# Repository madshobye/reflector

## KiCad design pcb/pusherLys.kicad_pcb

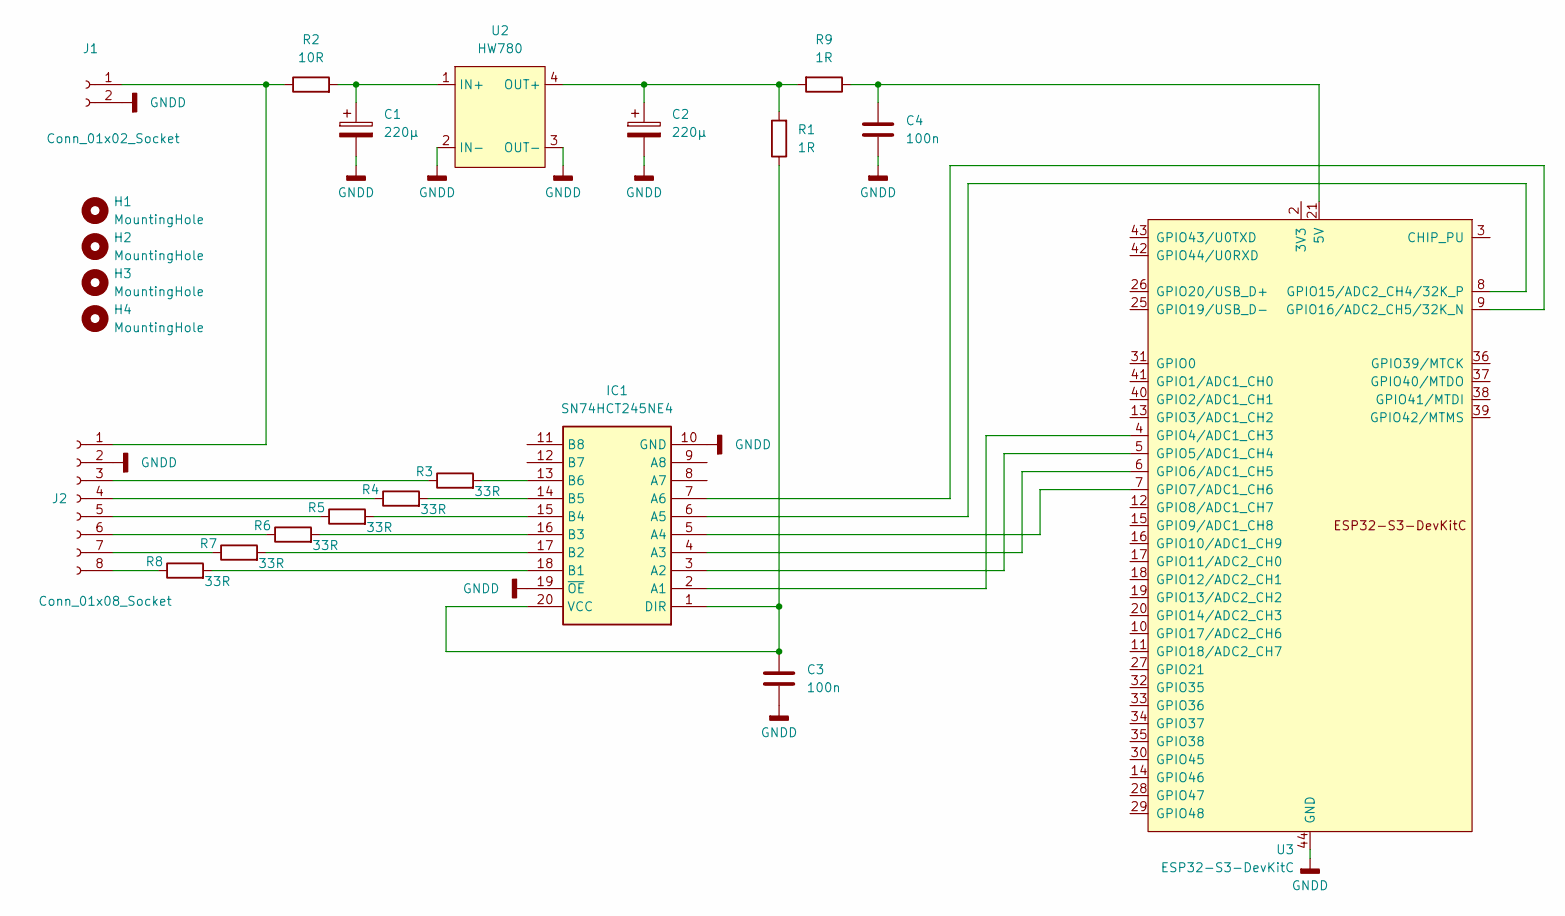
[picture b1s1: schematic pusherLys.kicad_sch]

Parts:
C1, C2: 220µ; CP_Radial_D8.0mm_P5.00mm
C3, C4: 100n; C_Disc_D5.0mm_W2.5mm_P5.00mm
H1, H2, H3, H4: MountingHole; MountingHole_3.5mm
IC1: SN74HCT245NE4; DIP-20_W7.62mm_LongPads; Mouser Part Number 595-SN74HCT245NE4
J1: Conn_01x02_Socket; TerminalBlock_MetzConnect_Type011_RT05502HBLC_1x02_P5.00mm_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
J2: Conn_01x08_Socket; TerminalBlock_MaiXu_MX126-5.0-08P_1x08_P5.00mm
R1, R9: 1R; R_Axial_DIN0207_L6.3mm_D2.5mm_P10.16mm_Horizontal
R2: 10R; R_Axial_DIN0207_L6.3mm_D2.5mm_P10.16mm_Horizontal
R3, R4, R5, R6, R7, R8: 33R; R_Axial_DIN0207_L6.3mm_D2.5mm_P10.16mm_Horizontal
U2: HW780
U3: ESP32-S3-DevKitC; ESP32-S3-DevKitC_WIDE

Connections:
GNDD: C1.2, C2.2, C3.2, C4.2, IC1.10 (GND), IC1.19 (~OE), J1.2, J2.2, U2.2 (IN-), U2.3 (OUT-), U3.22 (GND), U3.23 (GND), U3.24 (GND), U3.44 (GND)
unnamed: IC1.2 (A1), U3.4 (GPIO4/ADC1_CH3)
unnamed: IC1.3 (A2), U3.5 (GPIO5/ADC1_CH4)
unnamed: IC1.4 (A3), U3.6 (GPIO6/ADC1_CH5)
unnamed: IC1.5 (A4), U3.7 (GPIO7/ADC1_CH6)
unnamed: IC1.6 (A5), U3.8 (GPIO15/ADC2_CH4/32K_P)
unnamed: IC1.7 (A6), U3.9 (GPIO16/ADC2_CH5/32K_N)
unnamed: IC1.18 (B1), R8.2
unnamed: IC1.17 (B2), R7.2
unnamed: IC1.16 (B3), R6.2
unnamed: IC1.15 (B4), R5.2
unnamed: IC1.14 (B5), R4.2
unnamed: IC1.13 (B6), R3.2
unnamed: C3.1, IC1.1 (DIR), IC1.20 (VCC), R1.1
unnamed: J1.1, J2.1, R2.1
unnamed: J2.3, R3.1
unnamed: J2.4, R4.1
unnamed: J2.5, R5.1
unnamed: J2.6, R6.1
unnamed: J2.7, R7.1
unnamed: J2.8, R8.1
unnamed: C1.1, R2.2, U2.1 (IN+)
unnamed: C2.1, R1.2, R9.2, U2.4 (OUT+)
unnamed: U3.1 (3V3), U3.2 (3V3)
unnamed: C4.1, R9.1, U3.21 (5V)

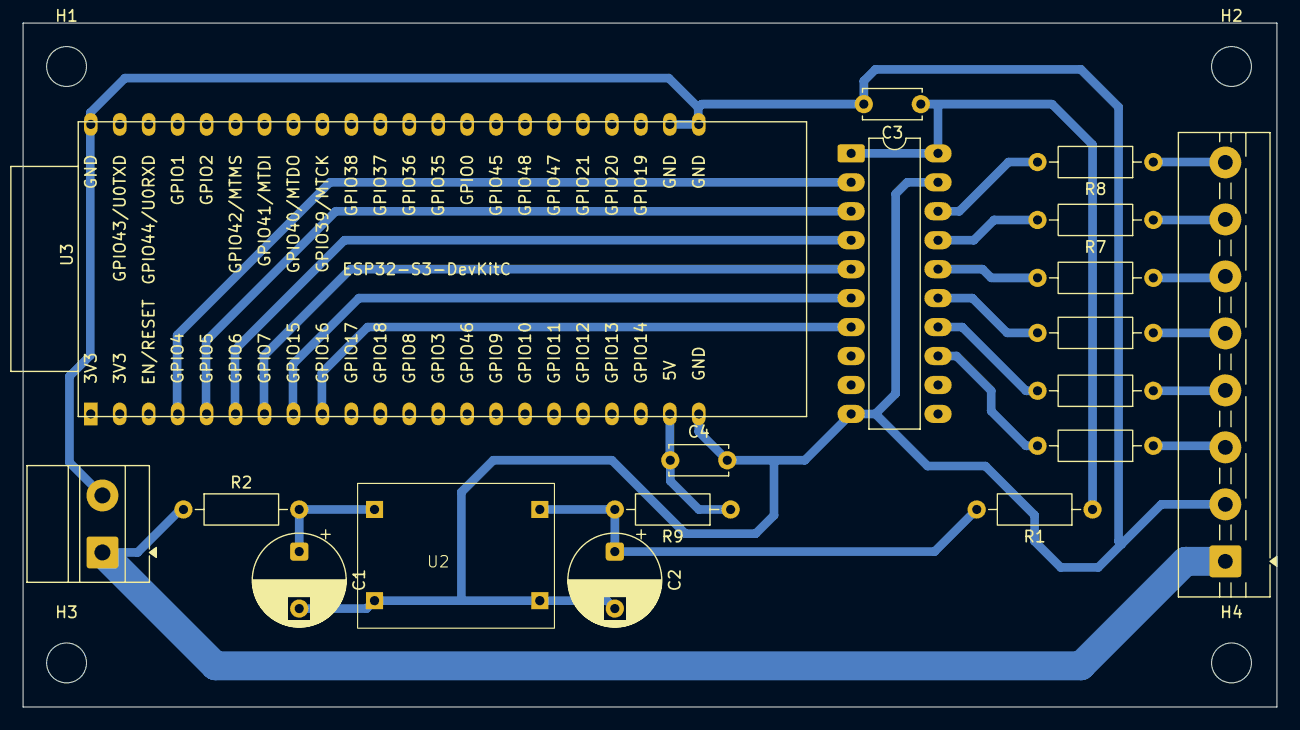
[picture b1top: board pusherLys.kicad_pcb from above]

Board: 2 copper layers, 110.0 x 60.0 mm, 22 parts (0 on the bottom side), 25 nets.

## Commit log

2026-03-11 x
    x
